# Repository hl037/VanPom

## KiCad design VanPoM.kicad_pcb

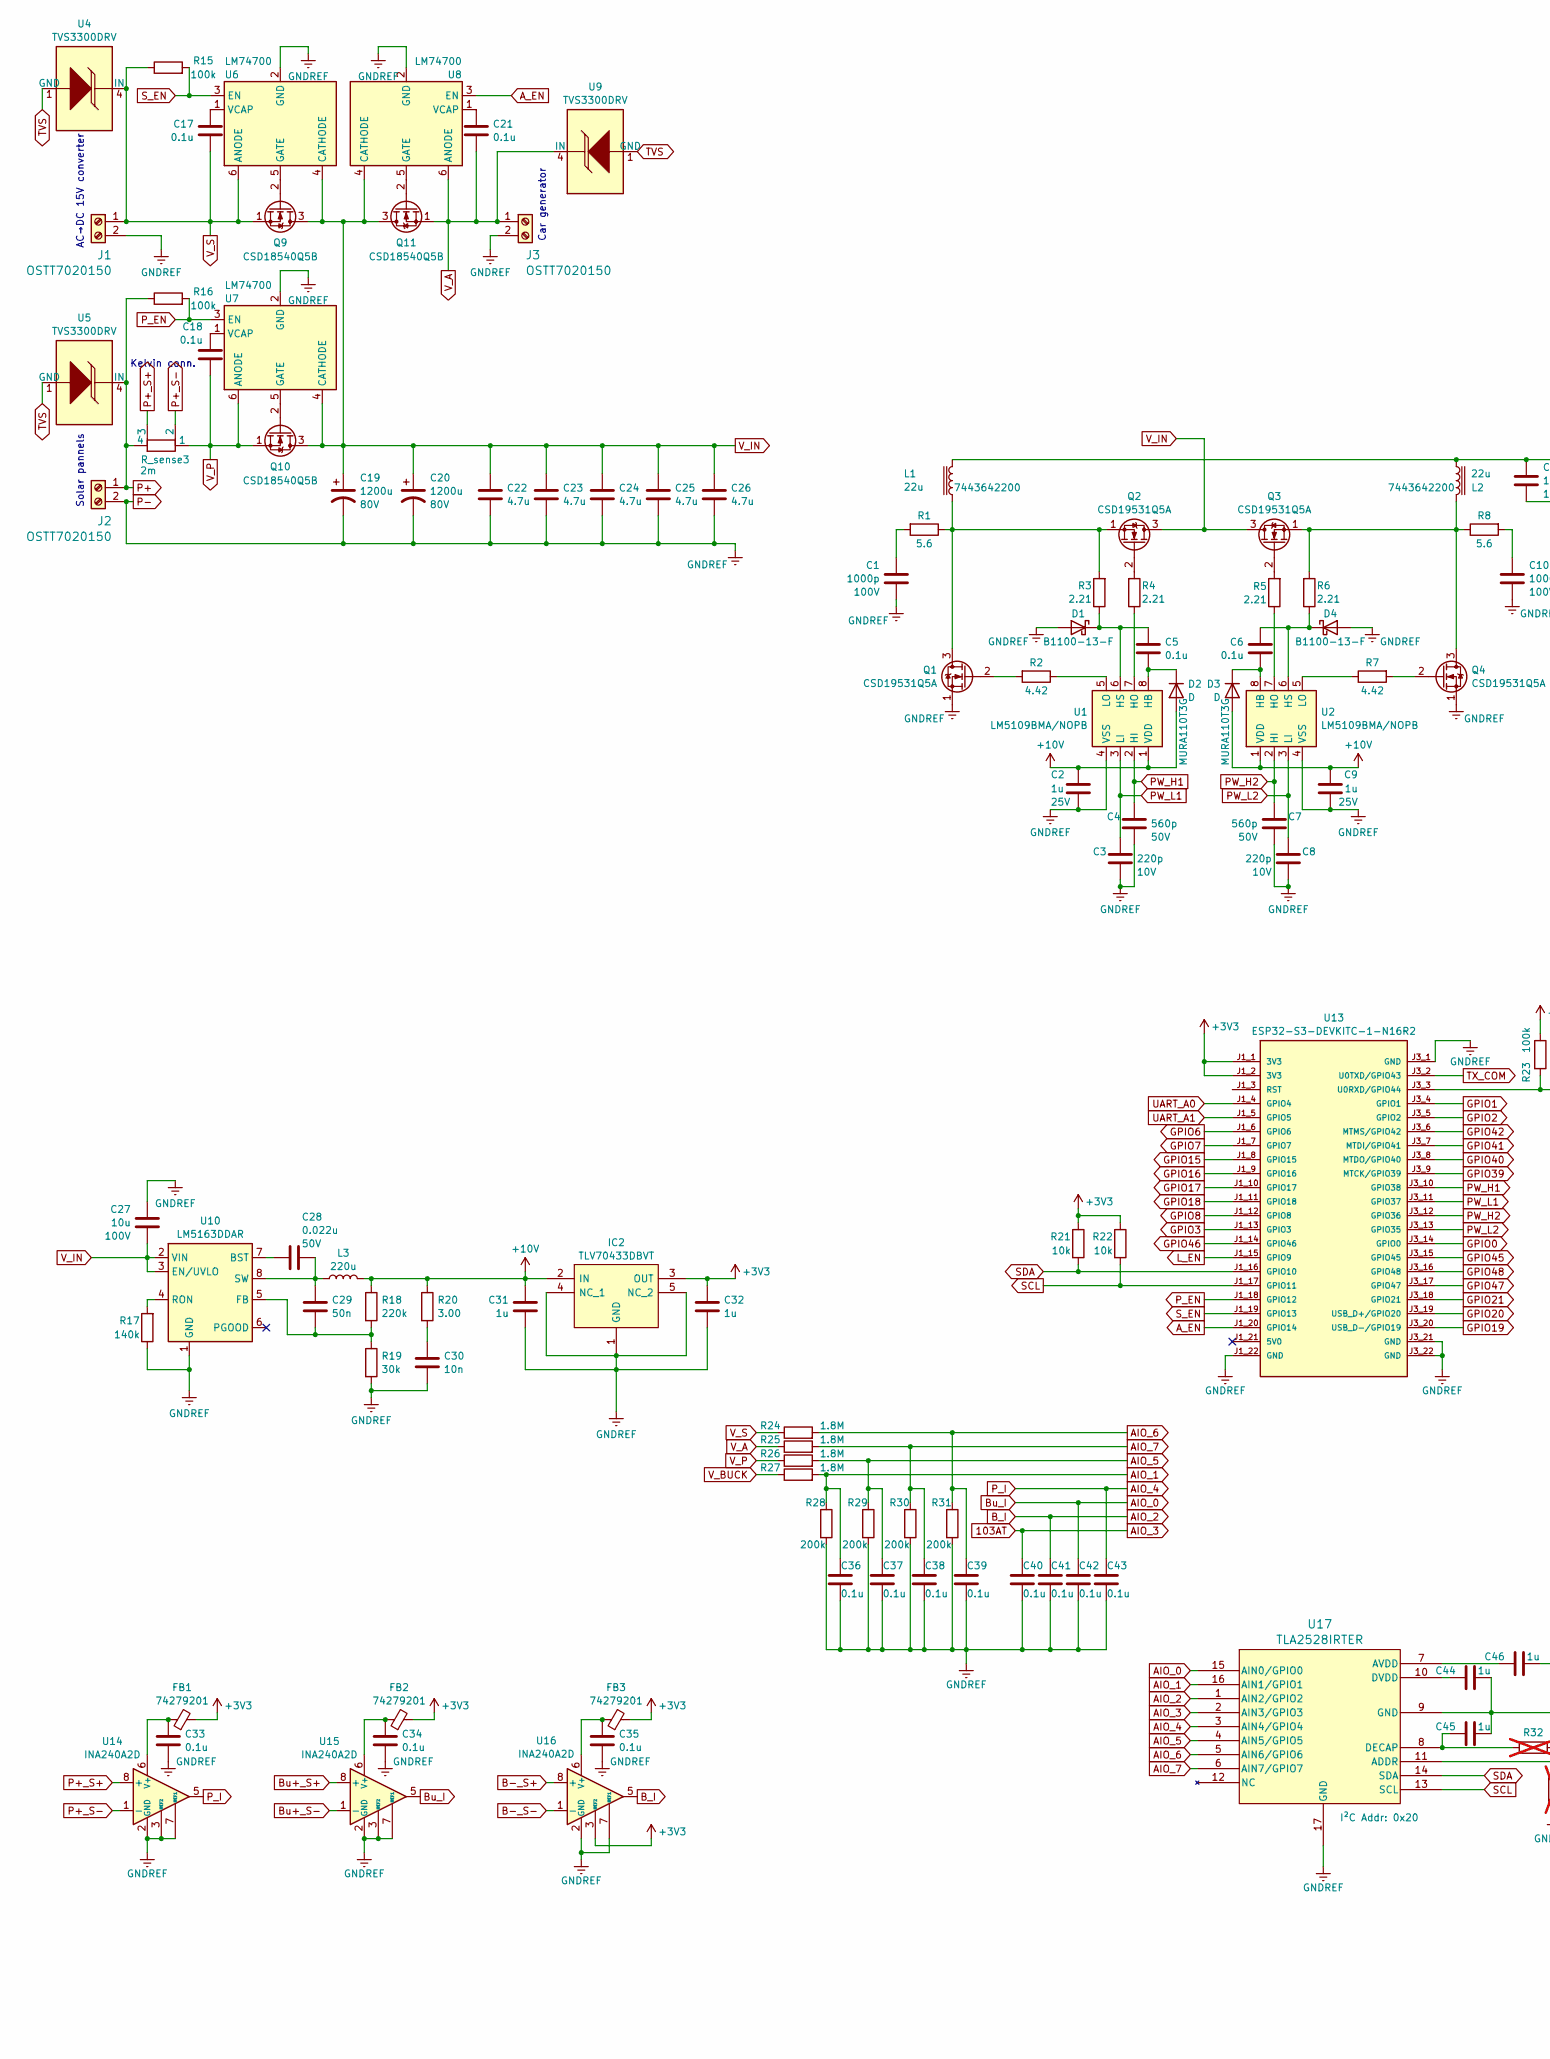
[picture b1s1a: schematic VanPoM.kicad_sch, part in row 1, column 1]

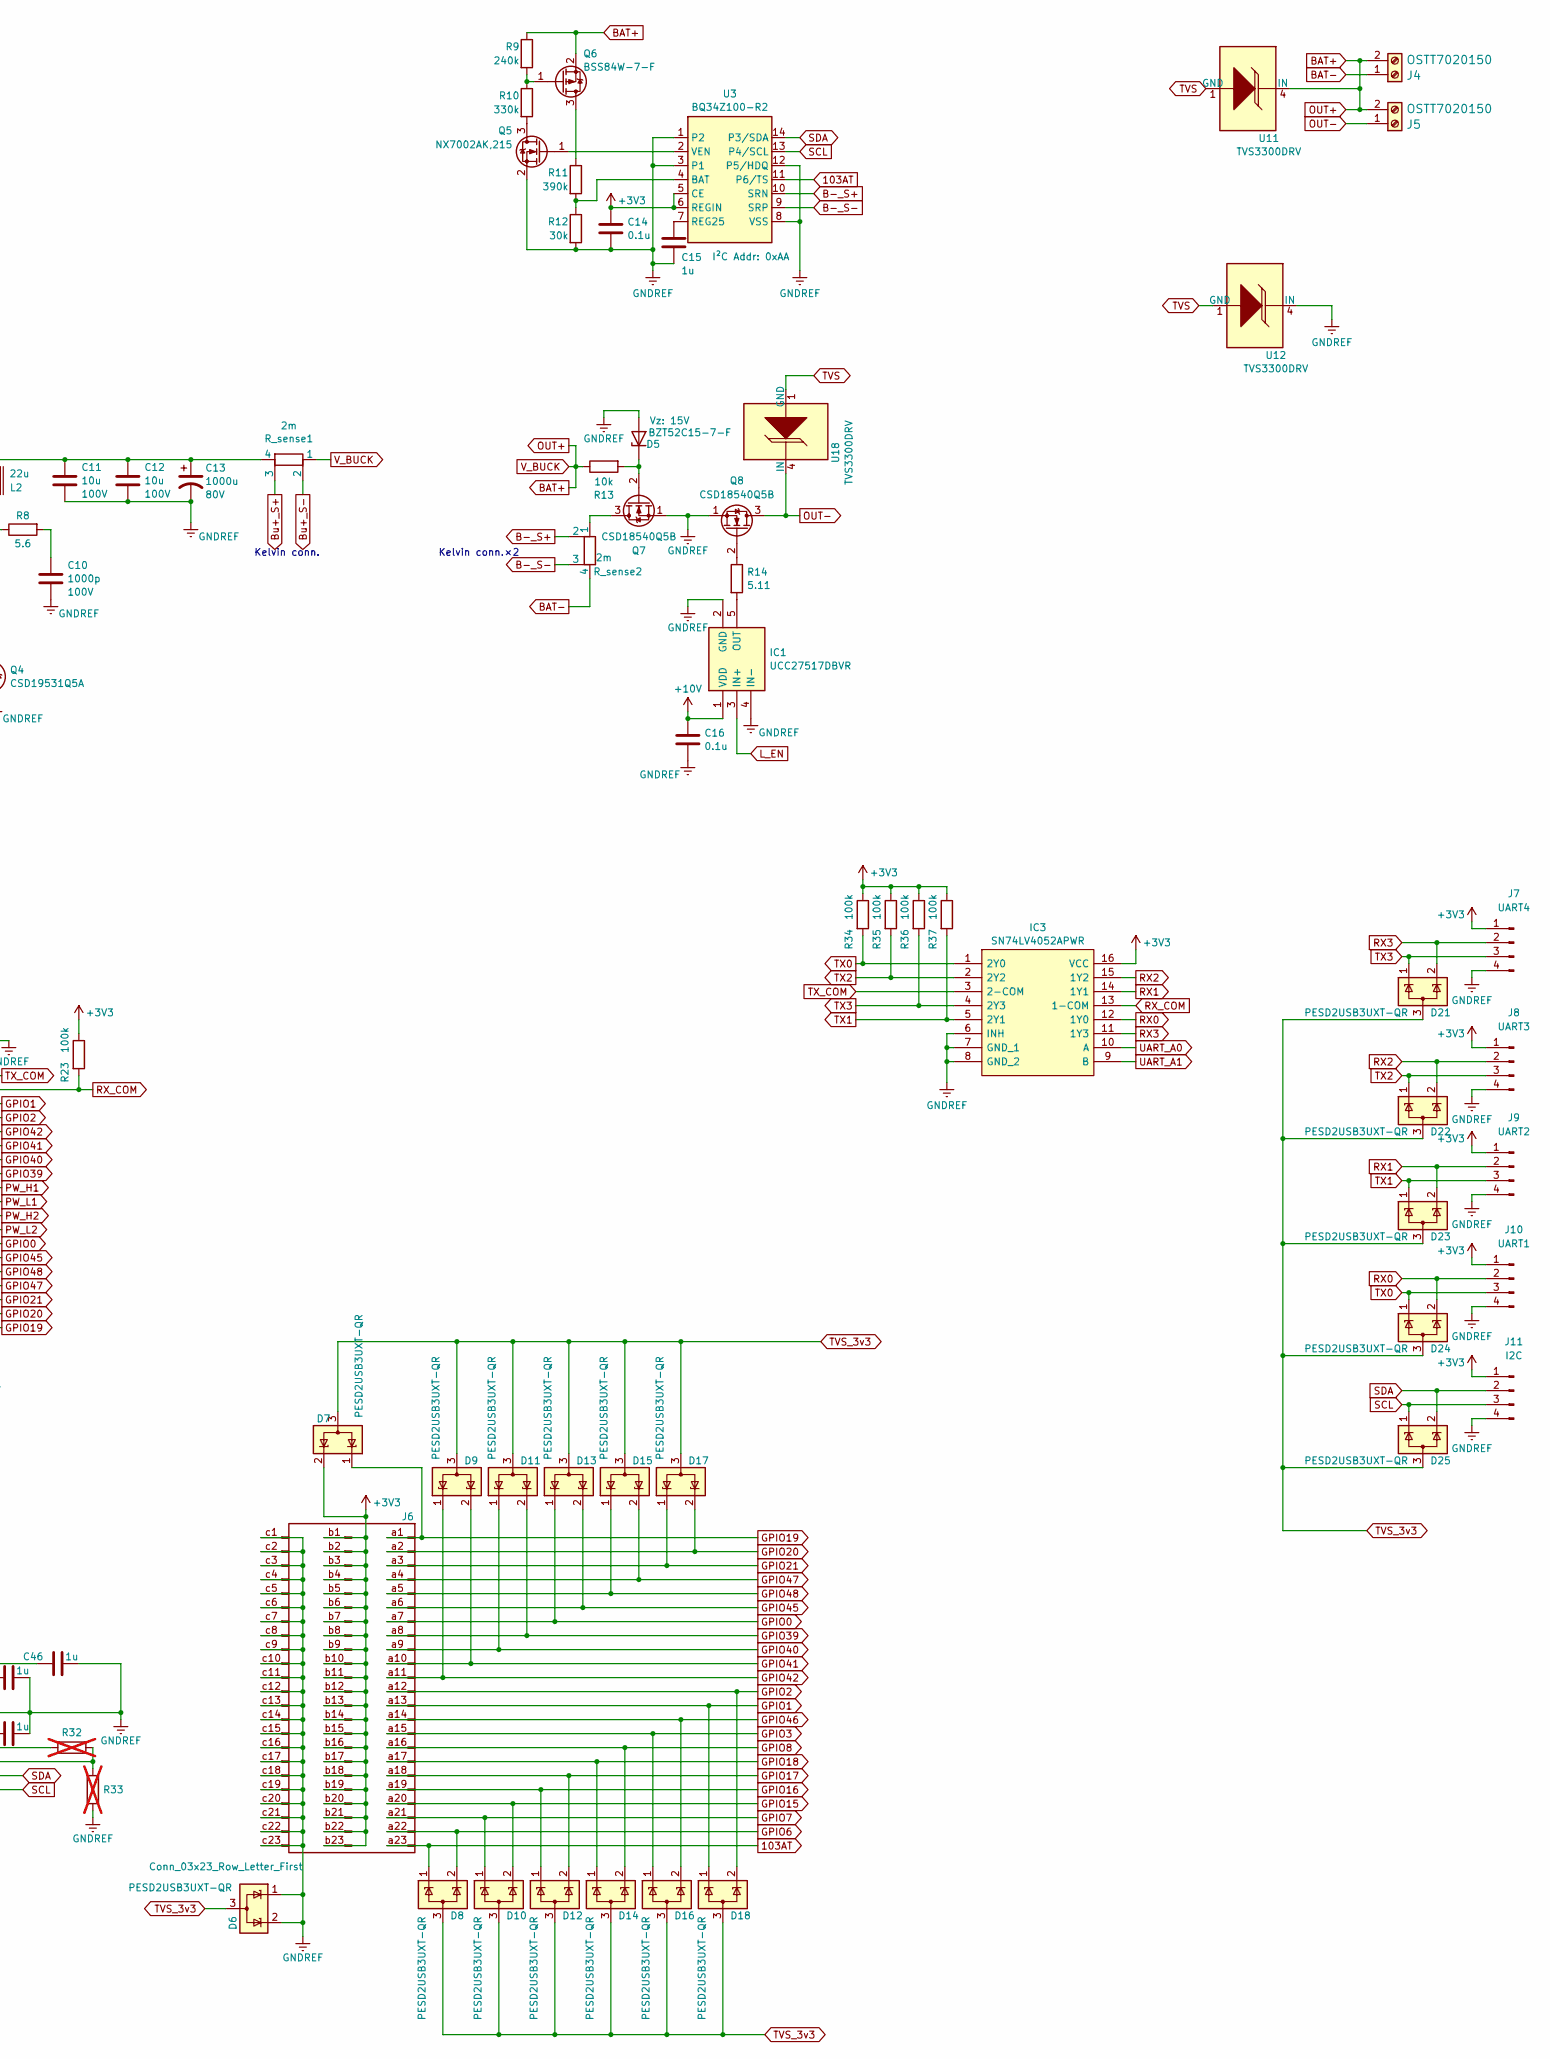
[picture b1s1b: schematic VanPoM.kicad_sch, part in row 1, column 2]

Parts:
C1, C10: 1000p; C_0603_1608Metric_Pad1.08x0.95mm_HandSolder; Voltage 100V; Manufacturer_Part_Number GRM188R72A102KA01J
C2, C9, C31: 1u; C_0805_2012Metric_Pad1.18x1.45mm_HandSolder; Voltage 25V; Manufacturer_Part_Number KGM21AR71E105JU
C3, C8: 220p; C_0603_1608Metric_Pad1.08x0.95mm_HandSolder; Voltage 10V; Manufacturer_Part_Number 885012206004
C4, C7: 560p; C_0402_1005Metric_Pad0.74x0.62mm_HandSolder; Voltage 50V; Manufacturer_Part_Number UMK105B7561KV-F
C5, C6, C14, C16, C17, C18, C21, C33, C34, C35, C36, C37, C38, C39, C40, C41, C42, C43: 0.1u; C_0603_1608Metric_Pad1.08x0.95mm_HandSolder; Manufacturer_Part_Number KGM15BR71H104JT
C11, C12, C27: 10u; C_1210_3225Metric_Pad1.33x2.70mm_HandSolder; Voltage 100V; Manufacturer_Part_Number GRM32EC72A106KE05K
C13: 1000u; CP_Radial_D16.0mm_P7.50mm; Voltage 80V; Manufacturer_Part_Number EKYB800ELL102MLP1S
C15, C32, C44, C45, C46: 1u; C_0402_1005Metric_Pad0.74x0.62mm_HandSolder; Manufacturer_Part_Number GRM155C81A105KA12D
C19, C20: 1200u; CP_Radial_D18.0mm_P7.50mm; Voltage 80V; Manufacturer_Part_Number EKY-800ELL122MM40S
C22, C23, C24, C25, C26: 4.7u; C_1206_3216Metric_Pad1.33x1.80mm_HandSolder; Manufacturer_Part_Number GRM31CC72A475KE11L
C28: 0.022u; C_1206_3216Metric_Pad1.33x1.80mm_HandSolder; Voltage 50V; Manufacturer_Part_Number C1206C223F3GEC7210
C29: 50n; C_0402_1005Metric_Pad0.74x0.62mm_HandSolder; Manufacturer_Part_Number GRM155R71E103JA01D
C30: 10n; C_0402_1005Metric_Pad0.74x0.62mm_HandSolder; Manufacturer_Part_Number GRM155R71E103JA01D
D1, D4: B1100-13-F; D_SMA; Manufacturer_Part_Number B1100-13-F
D2, D3: D; D_SMA; Manufacturer_Part_Number MURA110T3G
D5: BZT52C15-7-F; D_SOD-123; Manufacturer_Part_Number BZT52C15-7-F
D6, D7, D8, D9, D10, D11, D12, D13, D14, D15, D16, D17, D18, D21, D22, D23, D24, D25: PESD2USB3UXT-QR; SOT-23-3; Manufacturer_Part_Number PESD2USB3UXT-QR
FB1, FB2, FB3: 74279201; C_0805_2012Metric_Pad1.18x1.45mm_HandSolder; Manufacturer_Part_Number 74279201
IC1: UCC27517DBVR; SOT95P280X145-5N; Mouser Part Number 595-UCC27517DBVR
IC2: TLV70433DBVT; SOT95P280X145-5N; Mouser Part Number 595-TLV70433DBVT
IC3: SN74LV4052APWR; TSSOP-16_4.4x5mm_P0.65mm; Mouser Part Number 595-SN74LV4052APWR
J1, J2, J3, J4, J5: OSTT7020150; TerminalBlock_MetzConnect_Type073_RT02602HBLU_1x02_P5.08mm_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; Manufacturer_Part_Number EM290802
J6: Conn_03x23_Row_Letter_First; PinHeader_3x23_P2.54mm_Vertical; Manufacturer_Part_Number MTSW-127-07-T-T-110
J7: UART4; PinHeader_1x04_P2.54mm_Vertical; Manufacturer_Part_Number G800W304018EU
J8: UART3; PinHeader_1x04_P2.54mm_Vertical; Manufacturer_Part_Number G800W304018EU
J9: UART2; PinHeader_1x04_P2.54mm_Vertical; Manufacturer_Part_Number G800W304018EU
J10: UART1; PinHeader_1x04_P2.54mm_Vertical; Manufacturer_Part_Number G800W304018EU
J11: I2C; PinHeader_1x04_P2.54mm_Vertical; Manufacturer_Part_Number G800W304018EU
L1, L2: 22u; L_Wuerth_HCF-2818; Manufacturer_Part_Number 7443642200
L3: 220u; INDPM105103X500N; Manufacturer_Part_Number DR1050-221-R
Q1, Q2, Q3, Q4: CSD19531Q5A; VSONP-8-1EP_5x6_P1.27mm; Manufacturer_Part_Number CSD19531Q5A
Q5: NX7002AK,215; SOT-23-3; Manufacturer_Part_Number NX7002AK,215
Q6: BSS84W-7-F; SOT-323_SC-70_Handsoldering; Manufacturer_Part_Number BSS84W-7-F
Q7, Q8, Q9, Q10, Q11: CSD18540Q5B; VSONP-8-1EP_5x6_P1.27mm; Manufacturer_Part_Number CSD18540Q5B
R1, R8: 5.6; R_0805_2012Metric_Pad1.20x1.40mm_HandSolder; Manufacturer_Part_Number RK73H2ATTD5R60F
R2, R7: 4.42; R_0805_2012Metric_Pad1.20x1.40mm_HandSolder; Manufacturer_Part_Number RK73H2ATTD4R42F
R3, R4, R5, R6: 2.21; R_0805_2012Metric_Pad1.20x1.40mm_HandSolder; Manufacturer_Part_Number RK73H2ATTD2R21F
R9: 240k; R_0805_2012Metric_Pad1.20x1.40mm_HandSolder; Manufacturer_Part_Number RC0805FR-07240KL
R10: 330k; R_0805_2012Metric_Pad1.20x1.40mm_HandSolder; Manufacturer_Part_Number CRG0805F330K
R11: 390k; R_0805_2012Metric_Pad1.20x1.40mm_HandSolder; Manufacturer_Part_Number RC0805FR-10390KL
R12, R19: 30k; R_0805_2012Metric_Pad1.20x1.40mm_HandSolder; Manufacturer_Part_Number RK73H2ATTD3002F
R13, R21, R22: 10k; R_0805_2012Metric_Pad1.20x1.40mm_HandSolder; Manufacturer_Part_Number AC0805FR-7W10KL
R14: 5.11; R_0805_2012Metric_Pad1.20x1.40mm_HandSolder; Manufacturer_Part_Number RK73H2ATTD5R11F
R15, R16, R23, R34, R35, R36, R37: 100k; R_0805_2012Metric_Pad1.20x1.40mm_HandSolder; Manufacturer_Part_Number RK73H2ATTD1003F
R17: 140k; R_0805_2012Metric_Pad1.20x1.40mm_HandSolder; Manufacturer_Part_Number RK73H2ATTD1400F
R18: 220k; R_0805_2012Metric_Pad1.20x1.40mm_HandSolder; Manufacturer_Part_Number RK73H2ATTDD2203F
R20: 3.00; R_0805_2012Metric_Pad1.20x1.40mm_HandSolder; Manufacturer_Part_Number RK73H2ATTD3R00F
R24, R25, R26, R27: 1.8M; R_0805_2012Metric_Pad1.20x1.40mm_HandSolder; Manufacturer_Part_Number RK73H2ATTD1804F
R28, R29, R30, R31: 200k; R_0805_2012Metric_Pad1.20x1.40mm_HandSolder; Manufacturer_Part_Number RK73H2ATTDD2003F
R32, R33: R; R_0805_2012Metric_Pad1.20x1.40mm_HandSolder; not fitted
R_sense1, R_sense2, R_sense3: 2m; R_Shunt_Ohmite_LVK25-fixed; Manufacturer_Part_Number LVK25R002DER
U1, U2: LM5109BMA/NOPB; SOIC-8_3.9x4.9mm_P1.27mm; Manufacturer_Part_Number LM5109BMA/NOPB
U3: BQ34Z100-R2; TSSOP-14_4.4x5mm_P0.65mm; Manufacturer_Part_Number BQ34Z100-R2
U4, U5, U9, U11, U12, U18: TVS3300DRV; WSON-6-1EP_2x2mm_P0.65mm_EP1x1.6mm; Manufacturer_Part_Number TVS3300DRVR
U6, U7, U8: LM74700; SOT-23-6; Manufacturer_Part_Number LM74700QDBVTQ1
U10: LM5163DDAR; SOIC-8-1EP_3.9x4.9mm_P1.27mm_EP2.34x2.34mm_ThermalVias; Manufacturer_Part_Number LM5163DDAR
U13: ESP32-S3-DEVKITC-1-N16R2; XCVR_ESP32-S3-DEVKITC-1; PARTREV V1
U14, U15, U16: INA240A2D; SOIC-8_3.9x4.9mm_P1.27mm; Manufacturer_Part_Number INA240A2D
U17: TLA2528IRTER; WQFN16_RTE_TEX-L; Manufacturer_Part_Number TLA2528IRTER

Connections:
103AT: C40.1, D8.1 (K), J6.a23, U3.11 (P6/TS), U17.2 (AIN3/GPIO3)
+3V3: C14.1, C32.1, D7.2 (K), FB1.2, FB2.2, FB3.2, IC2.3 (OUT), IC3.16 (VCC), J6.b1, J6.b2, J6.b3, J6.b4, J6.b5, J6.b6, J6.b7, J6.b8, J6.b9, J6.b10, J6.b11, J6.b12, J6.b13, J6.b14, J6.b15, J6.b16, J6.b17, J6.b18, J6.b19, J6.b20, J6.b21, J6.b22, J6.b23, J7.1, J8.1, J9.1, J10.1, J11.1, R21.1, R22.1, R23.1, R34.1, R35.1, R36.1, R37.1, U3.5 (CE), U3.6 (REGIN), U13.J1_1 (3V3), U13.J1_2 (3V3), U16.3 (REF2)
+10V: C2.1, C9.1, C16.1, C31.1, D2.2 (A), D3.2 (A), IC1.1 (VDD), IC2.2 (IN), L3.2, R18.1, R20.1, U1.1 (VDD), U2.1 (VDD)
AIO_0: C42.1, U15.5, U17.15 (AIN0/GPIO0)
AIO_1: C36.1, R27.2, R28.1, U17.16 (AIN1/GPIO1)
AIO_2: C41.1, U16.5, U17.1 (AIN2/GPIO2)
AIO_4: C43.1, U14.5, U17.3 (AIN4/GPIO4)
AIO_5: C37.1, R26.2, R29.1, U17.4 (AIN5/GPIO5)
AIO_6: C39.1, R24.2, R31.1, U17.5 (AIN6/GPIO6)
AIO_7: C38.1, R25.2, R30.1, U17.6 (AIN7/GPIO7)
A_EN: U8.3 (EN), U13.J1_20 (GPIO14)
B-_S+: R_sense2.2, U3.10 (SRN), U16.8 (+)
B-_S-: R_sense2.3, U3.9 (SRP), U16.1 (-)
BAT+: J4.2, J5.2, Q6.2 (S), R9.1, R13.1, R27.1, R_sense1.1, U11.4 (IN), U11.5 (IN), U11.6 (IN)
BAT-: J4.1, R_sense2.4
Bu+_S+: R_sense1.3, U15.8 (+)
Bu+_S-: R_sense1.2, U15.1 (-)
GPIO0: D13.1 (K), J6.a7, U13.J3_14 (GPIO0)
GPIO1: D18.1 (K), J6.a13, U13.J3_4 (GPIO1)
GPIO2: D18.2 (K), J6.a12, U13.J3_5 (GPIO2)
GPIO3: D16.1 (K), J6.a15, U13.J1_13 (GPIO3)
GPIO6: D8.2 (K), J6.a22, U13.J1_6 (GPIO6)
GPIO7: D10.1 (K), J6.a21, U13.J1_7 (GPIO7)
GPIO8: D14.2 (K), J6.a16, U13.J1_12 (GPIO8)
GPIO15: D10.2 (K), J6.a20, U13.J1_8 (GPIO15)
GPIO16: D12.1 (K), J6.a19, U13.J1_9 (GPIO16)
GPIO17: D12.2 (K), J6.a18, U13.J1_10 (GPIO17)
GPIO18: D14.1 (K), J6.a17, U13.J1_11 (GPIO18)
GPIO19: D7.1 (K), J6.a1, U13.J3_20 (USB_D-/GPIO19)
GPIO20: D17.2 (K), J6.a2, U13.J3_19 (USB_D+/GPIO20)
GPIO21: D17.1 (K), J6.a3, U13.J3_18 (GPIO21)
GPIO39: D11.2 (K), J6.a8, U13.J3_9 (MTCK/GPIO39)
GPIO40: D11.1 (K), J6.a9, U13.J3_8 (MTDO/GPIO40)
GPIO41: D9.2 (K), J6.a10, U13.J3_7 (MTDI/GPIO41)
GPIO42: D9.1 (K), J6.a11, U13.J3_6 (MTMS/GPIO42)
GPIO45: D13.2 (K), J6.a6, U13.J3_15 (GPIO45)
GPIO46: D16.2 (K), J6.a14, U13.J1_14 (GPIO46)
GPIO47: D15.2 (K), J6.a4, U13.J3_17 (GPIO47)
GPIO48: D15.1 (K), J6.a5, U13.J3_16 (GPIO48)
L_EN: IC1.3 (IN+), U13.J1_15 (GPIO9)
unnamed: C1.1, R1.2
unnamed: C10.1, R8.2
unnamed: C11.1, C12.1, C13.1, L1.1, L2.2, R_sense1.4
unnamed: C30.1, R20.2
unnamed: C5.1, D1.1 (K), R3.1, U1.6 (HS)
unnamed: C5.2, D2.1 (K), U1.8 (HB)
unnamed: C6.2, D3.1 (K), U2.8 (HB)
unnamed: C6.1, D4.1 (K), R6.1, U2.6 (HS)
unnamed: D5.1 (K), Q7.2 (G), R13.2
unnamed: IC1.5 (OUT), R14.2
unnamed: L1.2, Q1.3 (D), Q2.1 (S), R1.1, R3.2
unnamed: L2.1, Q3.1 (S), Q4.3 (D), R6.2, R8.1
unnamed: Q1.2 (G), R2.2
unnamed: Q2.2 (G), R4.2
unnamed: Q3.2 (G), R5.2
unnamed: Q4.2 (G), R7.2
unnamed: Q5.3 (D), R10.2
unnamed: Q5.1 (G), U3.2 (VEN)
unnamed: Q6.3 (D), R11.1
unnamed: Q6.1 (G), R9.2, R10.1
unnamed: Q7.3 (D), R_sense2.1
unnamed: Q8.2 (G), R14.1
unnamed: R4.1, U1.7 (HO)
unnamed: R2.1, U1.5 (LO)
unnamed: R5.1, U2.7 (HO)
unnamed: R7.1, U2.5 (LO)
unnamed: R11.2, R12.1, U3.4 (BAT)
unnamed: C15.1, U3.7 (REG25)
unnamed: Q9.2 (G), U6.5 (GATE)
unnamed: C17.1, U6.1 (VCAP)
unnamed: Q10.2 (G), U7.5 (GATE)
unnamed: C18.1, U7.1 (VCAP)
unnamed: Q11.2 (G), U8.5 (GATE)
unnamed: C21.1, U8.1 (VCAP)
unnamed: C28.2, U10.7 (BST)
unnamed: C29.2, R18.2, R19.1, U10.5 (FB)
unnamed: R17.2, U10.4 (RON)
unnamed: C28.1, C29.1, L3.1, U10.8 (SW)
unnamed: C33.1, FB1.1, U14.6 (V+)
unnamed: C34.1, FB2.1, U15.6 (V+)
unnamed: C35.1, FB3.1, U16.6 (V+)
unnamed: R32.2, R33.2, U17.11 (ADDR)
unnamed: C46.1, U17.7 (AVDD)
unnamed: C45.1, R32.1, U17.8 (DECAP)
unnamed: C44.1, U17.10 (DVDD)
OUT-: J5.1, Q8.3 (D), U18.4 (IN), U18.5 (IN), U18.6 (IN)
P+: J2.1, R16.1, R_sense3.4, U5.4 (IN), U5.5 (IN), U5.6 (IN)
P+_S+: R_sense3.3, U14.8 (+)
P+_S-: R_sense3.2, U14.1 (-)
P-: C1.2, C2.2, C3.2, C4.2, C7.2, C8.2, C9.2, C10.2, C11.2, C12.2, C13.2, C14.2, C15.2, C16.2, C19.2, C20.2, C22.2, C23.2, C24.2, C25.2, C26.2, C27.1, C30.2, C31.2, C32.2, C33.2, C34.2, C35.2, C36.2, C37.2, C38.2, C39.2, C40.2, C41.2, C42.2, C43.2, C44.2, C45.2, C46.2, D1.2 (A), D4.2 (A), D5.2 (A), D6.1 (K), D6.2 (K), IC1.2 (GND), IC1.4 (IN-), IC2.1 (GND), IC2.4 (NC_1), IC2.5 (NC_2), IC3.6 (INH), IC3.7 (GND_1), IC3.8 (GND_2), J1.2, J2.2, J3.2, J6.c1, J6.c2, J6.c3, J6.c4, J6.c5, J6.c6, J6.c7 (Pin_b7), J6.c8 (Pin_b8), J6.c9, J6.c10, J6.c11, J6.c12, J6.c13, J6.c14, J6.c15, J6.c16, J6.c17, J6.c18, J6.c19, J6.c20, J6.c21, J6.c22, J6.c23, J7.4, J8.4, J9.4, J10.4, J11.4, Q1.1 (S), Q4.1 (S), Q5.2 (S), Q7.1 (S), Q8.1 (S), R12.2, R17.1, R19.2, R28.2, R29.2, R30.2, R31.2, R33.1, U1.4 (VSS), U2.4 (VSS), U3.1 (P2), U3.3 (P1), U3.8 (VSS), U3.12 (P5/HDQ), U6.2 (GND), U7.2 (GND), U8.2 (GND), U10.1 (GND), U12.4 (IN), U12.5 (IN), U12.6 (IN), U13.J1_22 (GND), U13.J3_1 (GND), U13.J3_21 (GND), U13.J3_22 (GND), U14.2 (GND), U14.3 (REF2), U14.4 (GND), U14.7 (REF1), U15.2 (GND), U15.3 (REF2), U15.4 (GND), U15.7 (REF1), U16.2 (GND), U16.4 (GND), U16.7 (REF1), U17.9 (GND), U17.17 (GND)
PW_H1: C4.1, U1.2 (HI), U13.J3_10 (GPIO38)
PW_H2: C7.1, U2.2 (HI), U13.J3_12 (GPIO36)
PW_L1: C3.1, U1.3 (LI), U13.J3_11 (GPIO37)
PW_L2: C8.1, U2.3 (LI), U13.J3_13 (GPIO35)
P_EN: R16.2, U7.3 (EN), U13.J1_18 (GPIO12)
RX0: D24.2 (K), IC3.12 (1Y0), J10.2
RX1: D23.2 (K), IC3.14 (1Y1), J9.2
RX2: D22.2 (K), IC3.15 (1Y2), J8.2
RX3: D21.2 (K), IC3.11 (1Y3), J7.2
RX_COM: IC3.13 (1-COM), R23.2, U13.J3_3 (U0RXD/GPIO44)
SCL: D25.1 (K), J11.3, R22.2, U3.13 (P4/SCL), U13.J1_17 (GPIO11), U17.13 (SCL)
SDA: D25.2 (K), J11.2, R21.2, U3.14 (P3/SDA), U13.J1_16 (GPIO10), U17.14 (SDA)
S_EN: R15.2, U6.3 (EN), U13.J1_19 (GPIO13)
TVS: U4.1 (GND), U4.2 (GND), U4.3 (GND), U4.7 (GND), U5.1 (GND), U5.2 (GND), U5.3 (GND), U5.7 (GND), U9.1 (GND), U9.2 (GND), U9.3 (GND), U9.7 (GND), U11.1 (GND), U11.2 (GND), U11.3 (GND), U11.7 (GND), U12.1 (GND), U12.2 (GND), U12.3 (GND), U12.7 (GND), U18.1 (GND), U18.2 (GND), U18.3 (GND), U18.7 (GND)
TVS_3v3: D6.3 (A), D7.3 (A), D8.3 (A), D9.3 (A), D10.3 (A), D11.3 (A), D12.3 (A), D13.3 (A), D14.3 (A), D15.3 (A), D16.3 (A), D17.3 (A), D18.3 (A), D21.3 (A), D22.3 (A), D23.3 (A), D24.3 (A), D25.3 (A)
TX0: D24.1 (K), IC3.1 (2Y0), J10.3, R34.2
TX1: D23.1 (K), IC3.5 (2Y1), J9.3, R37.2
TX2: D22.1 (K), IC3.2 (2Y2), J8.3, R35.2
TX3: D21.1 (K), IC3.4 (2Y3), J7.3, R36.2
TX_COM: IC3.3 (2-COM), U13.J3_2 (U0TXD/GPIO43)
UART_A0: IC3.10 (A), U13.J1_4 (GPIO4)
UART_A1: IC3.9 (B), U13.J1_5 (GPIO5)
V_A: C21.2, J3.1, Q11.1 (S), R25.1, U8.6 (ANODE), U9.4 (IN), U9.5 (IN), U9.6 (IN)
V_IN: C19.1, C20.1, C22.1, C23.1, C24.1, C25.1, C26.1, C27.2, Q2.3 (D), Q3.3 (D), Q9.3 (D), Q10.3 (D), Q11.3 (D), U6.4 (CATHODE), U7.4 (CATHODE), U8.4 (CATHODE), U10.2 (VIN), U10.3 (EN/UVLO)
V_P: C18.2, Q10.1 (S), R26.1, R_sense3.1, U7.6 (ANODE)
V_S: C17.2, J1.1, Q9.1 (S), R15.1, R24.1, U4.4 (IN), U4.5 (IN), U4.6 (IN), U6.6 (ANODE)

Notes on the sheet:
Kelvin conn.
Kelvin conn.×2
Solar pannels
Car generator
AC→DC 15V converter

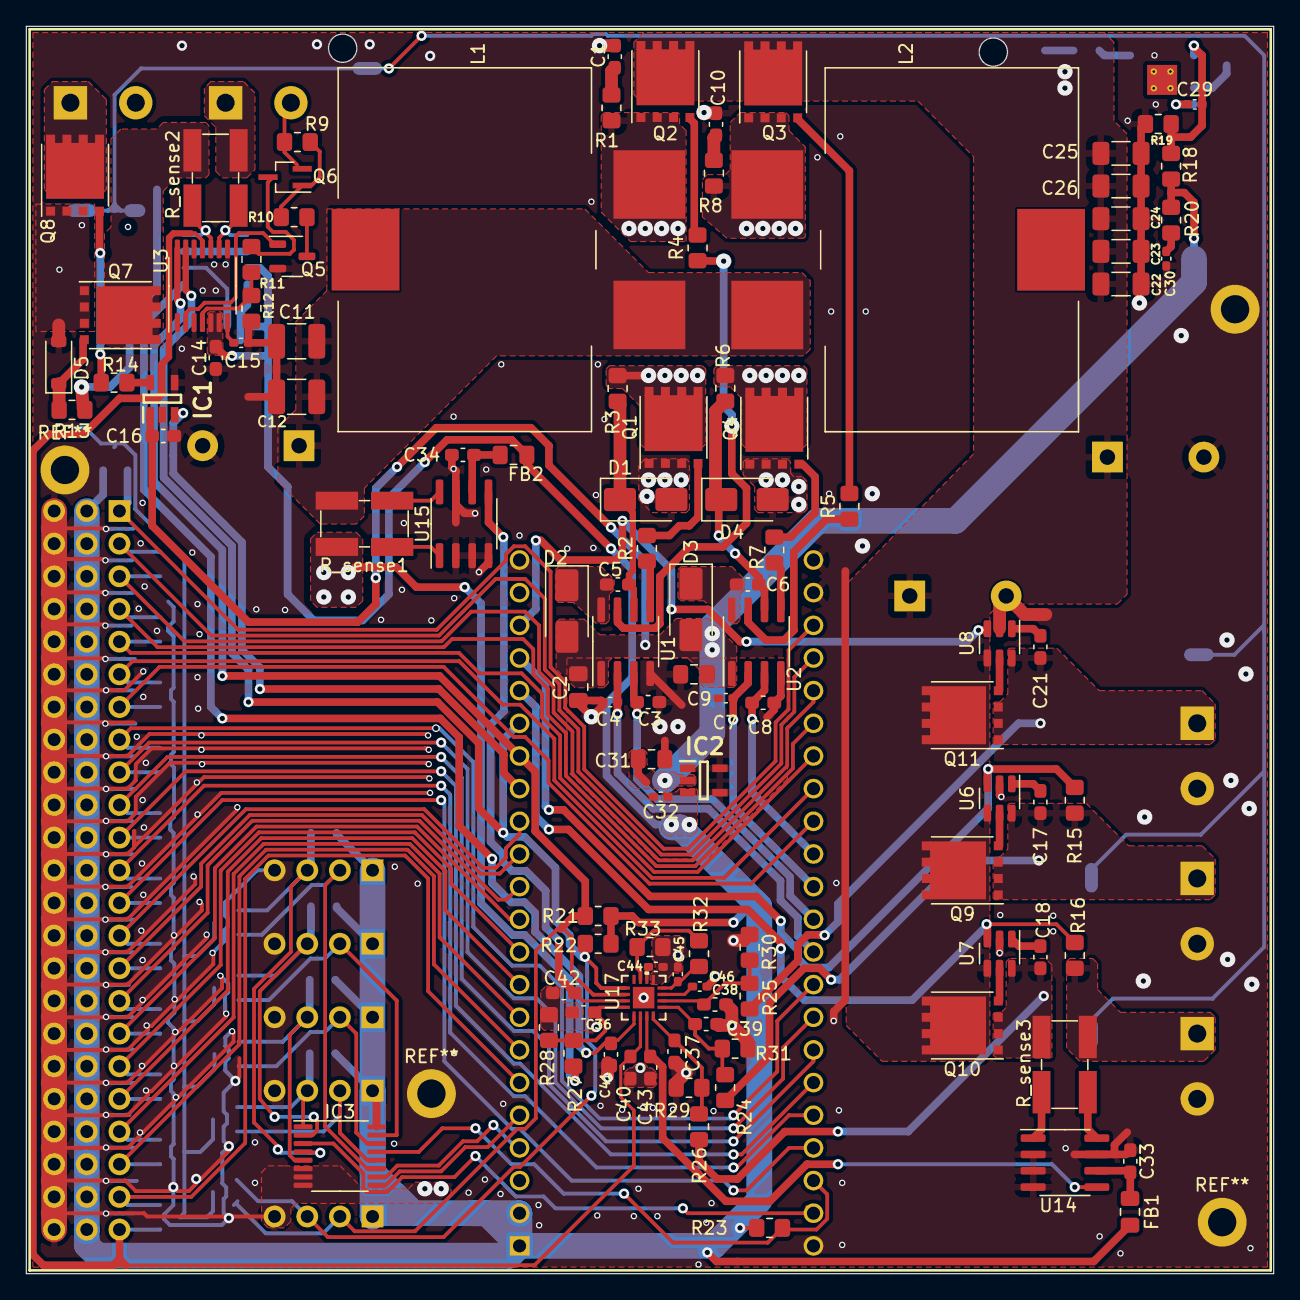
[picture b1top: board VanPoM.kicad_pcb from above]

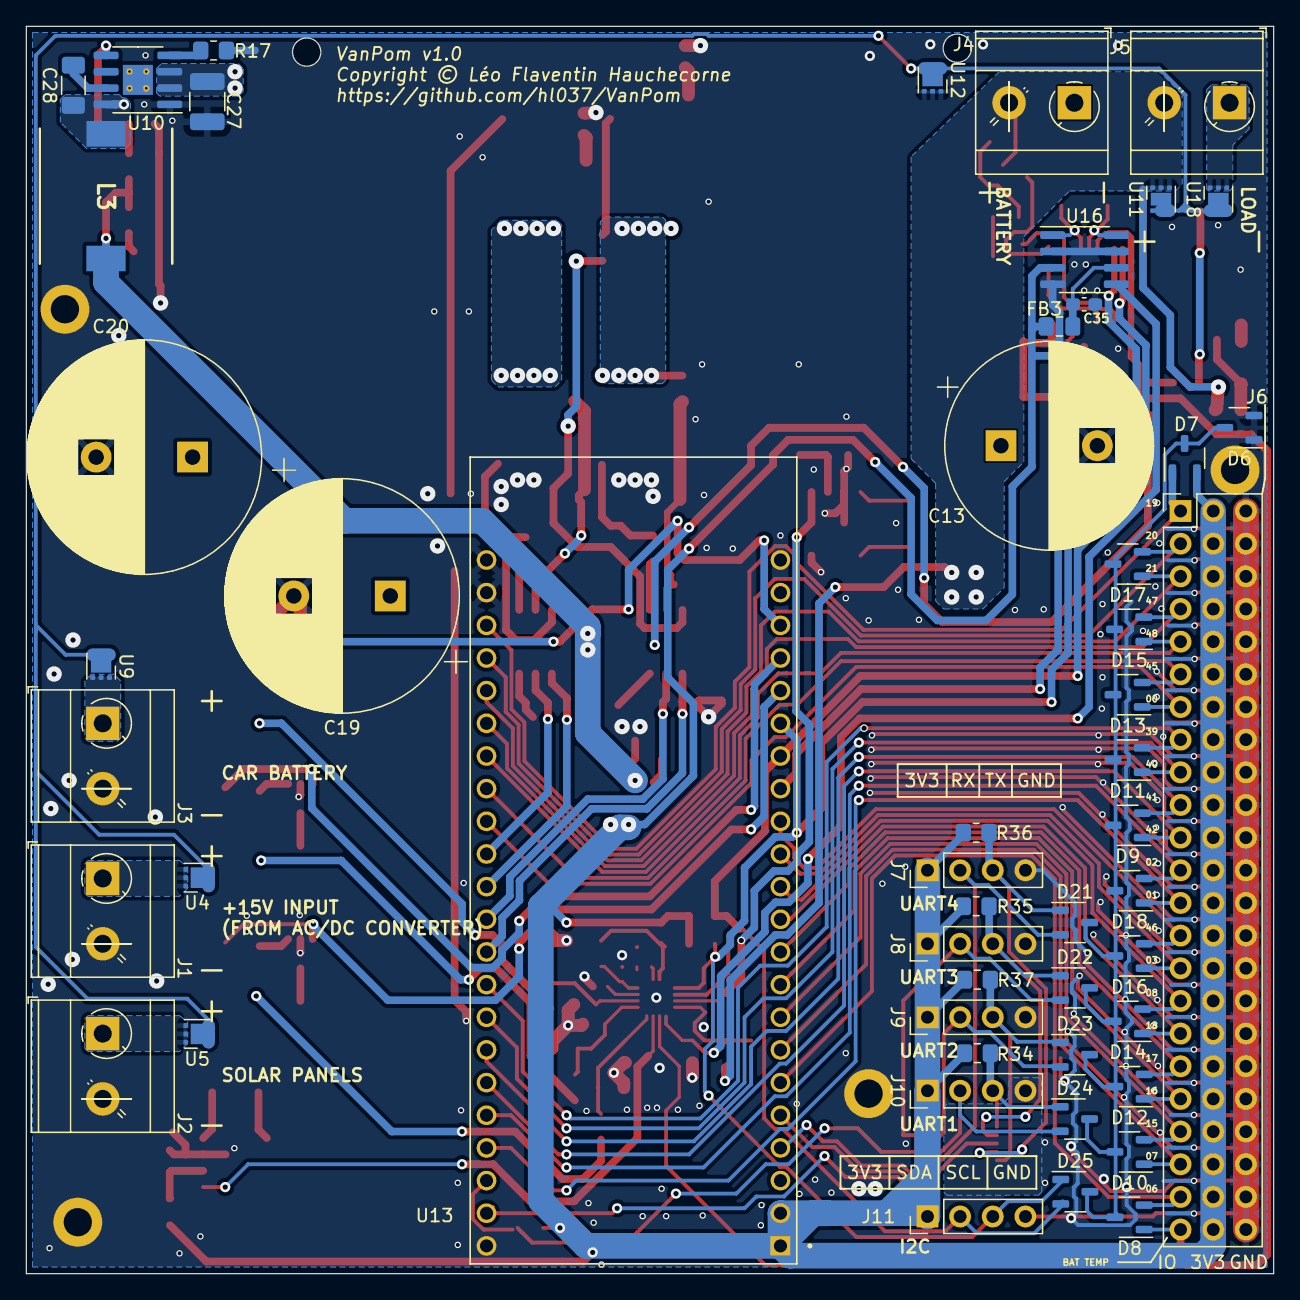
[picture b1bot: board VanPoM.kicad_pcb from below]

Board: 2 copper layers, 97.0 x 97.0 mm, 158 parts (51 on the bottom side), 116 nets.

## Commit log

2023-10-27 init
2023-11-10 Added doc since TI removed it...
2023-11-10 + pull ups I²C; f sda scl swaped on U12; + I²C addrs; + I²C connector
2023-11-10 + UART pull-ups
2023-11-24 +++ PCB; f many small things
2023-11-24 schema
2023-11-24 + screen shots
2023-11-27 + Thermal reliefs

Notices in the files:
VanPoM.kicad_pcb:
Copyright © Léo Flaventin Hauchecorne
